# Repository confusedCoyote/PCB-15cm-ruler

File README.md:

# PCB-15cm-ruler
A Printed Circuit Board ruler with some helpful hints

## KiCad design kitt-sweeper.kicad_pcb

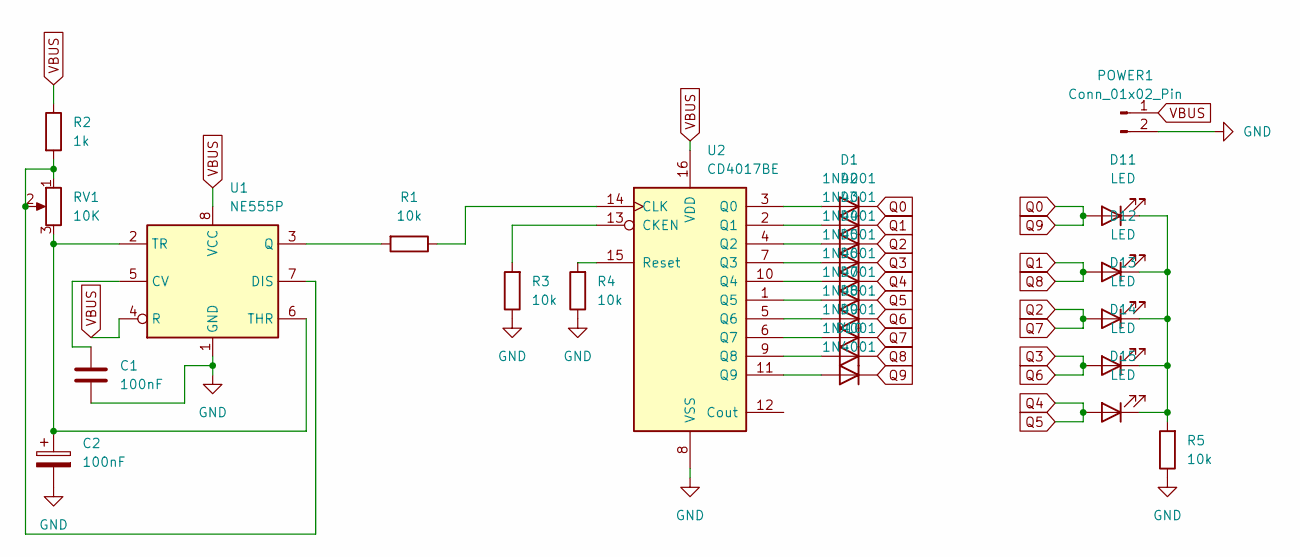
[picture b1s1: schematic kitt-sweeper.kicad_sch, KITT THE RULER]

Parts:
C1: 100nF; C_Disc_D3.4mm_W2.1mm_P2.50mm
C2: 100nF; CP_Radial_D4.0mm_P1.50mm
D1, D2, D3, D4, D5, D6, D7, D8, D9, D10: 1N4001; D_DO-41_SOD81_P10.16mm_Horizontal
D11, D12, D13, D14, D15: LED; LED_D3.0mm
POWER1: Conn_01x02_Pin; SolderWire-1sqmm_1x02_P5.4mm_D1.4mm_OD2.7mm
R1, R3, R4, R5: 10k; R_Axial_DIN0207_L6.3mm_D2.5mm_P10.16mm_Horizontal
R2: 1k; R_Axial_DIN0207_L6.3mm_D2.5mm_P10.16mm_Horizontal
RV1: 10K; Potentiometer_Runtron_RM-063_Horizontal
U1: NE555P; DIP-8_W7.62mm
U2: CD4017BE; DIP-16_W7.62mm

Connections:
GND: C1.2, C2.2, POWER1.2, R3.1, R4.1, R5.1, U1.1 (GND), U2.8 (VSS)
unnamed: D1.2 (A), U2.3 (Q0)
unnamed: D2.2 (A), U2.2 (Q1)
unnamed: D3.2 (A), U2.4 (Q2)
unnamed: D4.2 (A), U2.7 (Q3)
unnamed: D5.2 (A), U2.10 (Q4)
unnamed: D6.2 (A), U2.1 (Q5)
unnamed: D7.2 (A), U2.5 (Q6)
unnamed: D8.2 (A), U2.6 (Q7)
unnamed: D9.2 (A), U2.9 (Q8)
unnamed: D10.2 (A), U2.11 (Q9)
unnamed: D11.1 (K), D12.1 (K), D13.1 (K), D14.1 (K), D15.1 (K), R5.2
unnamed: C1.1, U1.5 (CV)
unnamed: R2.2, RV1.1, RV1.2, U1.7 (DIS)
unnamed: R1.2, U1.3 (Q)
unnamed: C2.1, RV1.3, U1.2 (TR), U1.6 (THR)
unnamed: R3.2, U2.13 (CKEN)
unnamed: R1.1, U2.14 (CLK)
unnamed: R4.2, U2.15 (Reset)
Q0: D1.1 (K), D10.1 (K), D11.2 (A)
Q1: D2.1 (K), D9.1 (K), D12.2 (A)
Q2: D3.1 (K), D8.1 (K), D13.2 (A)
Q3: D4.1 (K), D7.1 (K), D14.2 (A)
Q4: D5.1 (K), D6.1 (K), D15.2 (A)
VBUS: POWER1.1, R2.1, U1.4 (R), U1.8 (VCC), U2.16 (VDD)

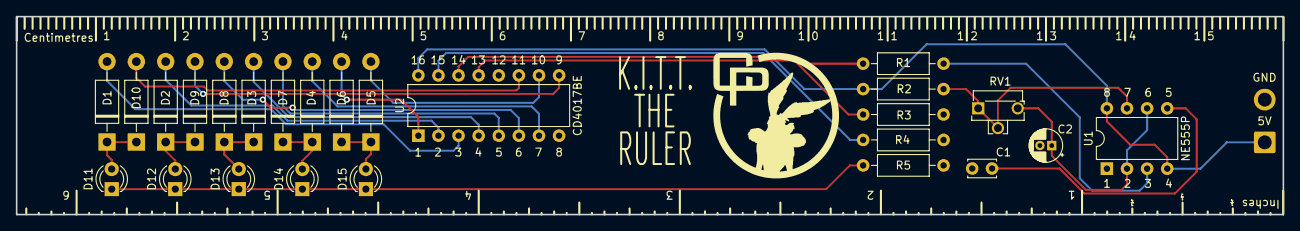
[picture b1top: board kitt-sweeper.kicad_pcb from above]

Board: 2 copper layers, 160.0 x 25.0 mm, 26 parts (0 on the bottom side), 25 nets.

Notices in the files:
kitt-sweeper.kicad_pcb:
© COYOTE PRODUCTIONS
